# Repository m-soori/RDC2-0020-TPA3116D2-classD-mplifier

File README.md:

<p></p>

<p>Усилитель НЧ собран на микросхеме TPA3116D2.</p>
<p></p>
<h2>Технические характеристики.</h2>
<p>Мощность на нагрузке 4 Ом. при U пит. 21В. – 2 x 50 Вт. (BTL), 100 Вт. (PBTL)<br/>Уровень сигнала на входе. - 0,8 … 2В.<br/>Отношение сигнал/шум. - 102 dB<br/>Коэффициент гармоник на половине мощности 25Вт. -  0,1%<br/>Напряжение питания – 4,5 В … 26 В.</p>
<p>Схема позволяет включать микросхему в двух режимах: </p>
<p>1. Мостовой BTL. В этом включении можно получить 2 канала по 50 Вт.<br/>2. Параллельно – мостовой (PBTL). Так как в этом режиме два канала BTL включены ещё и параллельно, то на выходе получаем один канал с удвоенной мощностью – 100 Вт.</p>
<p>На схемах ниже показаны все необходимые изменения для обоих режимов. </p>
<p>1. Подготовка платы для работы в мостовом режиме. Стерео 50 Вт.<br/>Собранный усилитель работает в мостовом режиме. Но если вы подаете на него сигнал по не симметричной линии, установите перемычки P7 и P12. Больше никаких перемычек устанавливать не надо. </p>
<p>2. Подготовка платы для работы в параллельно-мостовом режиме. Один канал 100 Вт.<br/>Установите перемычки P14, P15 и соедините перемычкой выходы усилителя P3 с P4 и P8 с P11.<br/>Теперь ваш усилитель будет работать в параллельно-мостовом режиме и выдавать 100 Вт.  Громкоговоритель подключайте к P6 и P8. Сигнал подавайте на вход правого канала.</p>
<p>Режим BTL</p>
<p></p>
<p>Режим PBTL</p>
<p></p>
<p>Подбором резисторов R5 и R8 можно подобрать уровень усиления и входное сопротивление, а также перевести усилитель в режимы ведущего (master) или ведомого (slave)</p>
<p></p>
<p>Усилитель имеет очень высокий КПД > 90%, поэтому он не очень требователен к теплоотводу. В качестве радиатора можно использовать, <a href="/product0/9000398392" class="link">например этот</a>. Форма, крепежные отверстия и размеры, которого сделаны специально для этого модуля. К тому же он имеет золотое покрытие, что внешне очень привлекательно.</p>
<p>Радиатор</p>
<p></p>
<p>Это открытый проект! Лицензия, под которой он распространяется – <a href="https://creativecommons.org/licenses/by-sa/3.0/"  class="link">Creative Commons - Attribution - Share Alike</a> license.</p>

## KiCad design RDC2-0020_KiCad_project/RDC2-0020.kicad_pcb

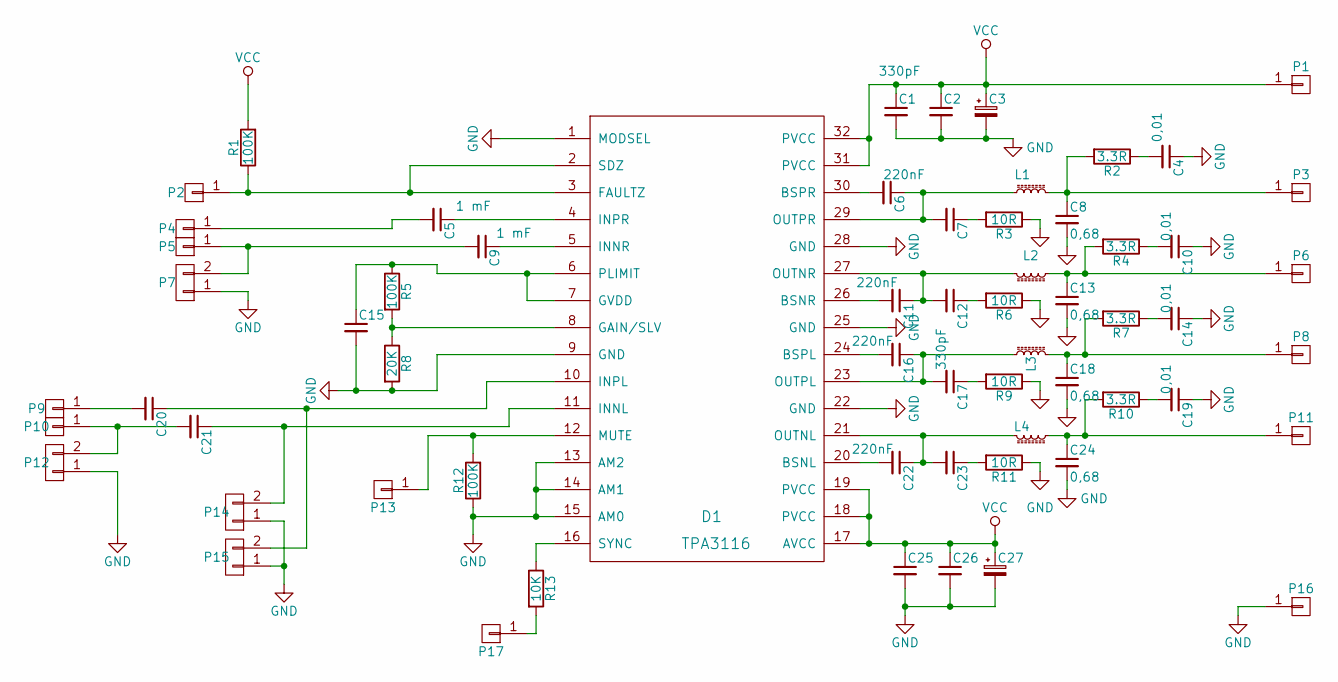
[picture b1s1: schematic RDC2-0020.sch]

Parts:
C1, C7, C12, C17, C23, C25: 330pF; C_1206
C2, C26: 0,1; C_0603
C3: 220mF; C_Radial_D8_L11.5_P3.5
C4, C10, C14, C19: 0,01; C_0805
C5, C9: 1 mF; C_0603
C6, C11, C16, C22: 220nF; C_0805
C8, C13, C18, C24: 0,68; C_1206
C15: C_Small; C_0805
C20, C21: C_Small; C_0603
C27: 220pF; C_Radial_D8_L11.5_P3.5
D1: TPA3116; TSSOP32
L1, L2, L3, L4: L_Core_Ferrite_Small; IND_12x12mm_h6mm
P1, P16: CONN_01X01; MountingHole_3.2mm_M3_Pad
P2, P3, P4, P5, P6, P8, P9, P10, P11, P13, P17: CONN_01X01; Pin_Header_Straight_1x01
P7, P12, P14, P15: CONN_01X02; JUMPER_ON
R1, R5, R12: 100K; R_0603
R2, R4, R7, R10: 3.3R; R_0603
R3, R6, R9, R11: 10R; R_0603
R8: 20K; R_0603
R13: 10K; R_0603

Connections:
GND: C1.2, C2.2, C3.2, C4.1, C8.2, C10.1, C13.2, C14.1, C15.2, C18.2, C19.1, C24.2, C25.2, C26.2, C27.2, D1.1 (MODSEL), D1.9 (GND), D1.13 (AM2), D1.14 (AM1), D1.15 (AM0), D1.22 (GND), D1.25 (GND), D1.28 (GND), P7.1, P12.1, P14.1, P15.1, P16.1, R3.1, R6.1, R8.2, R9.1, R11.1, R12.1
unnamed: C4.2, R2.1
unnamed: C5.1, D1.4 (INPR)
unnamed: C5.2, P4.1
unnamed: C6.1, C7.2, D1.29 (OUTPR), L1.1
unnamed: C6.2, D1.30 (BSPR)
unnamed: C7.1, R3.2
unnamed: C8.1, L1.2, P3.1, R2.2
unnamed: C9.1, D1.5 (INNR)
unnamed: C9.2, P5.1, P7.2
unnamed: C10.2, R4.1
unnamed: C11.1, C12.2, D1.27 (OUTNR), L2.2
unnamed: C11.2, D1.26 (BSNR)
unnamed: C12.1, R6.2
unnamed: C13.1, L2.1, P6.1, R4.2
unnamed: C14.2, R7.1
unnamed: C15.1, D1.6 (PLIMIT), D1.7 (GVDD), R5.1
unnamed: C16.1, C17.2, D1.23 (OUTPL), L3.1
unnamed: C16.2, D1.24 (BSPL)
unnamed: C17.1, R9.2
unnamed: C18.1, L3.2, P8.1, R7.2
unnamed: C19.2, R10.1
unnamed: C20.1, D1.10 (INPL), P15.2
unnamed: C20.2, P9.1
unnamed: C21.1, D1.11 (INNL), P14.2
unnamed: C21.2, P10.1, P12.2
unnamed: C22.1, C23.2, D1.21 (OUTNL), L4.2
unnamed: C22.2, D1.20 (BSNL)
unnamed: C23.1, R11.2
unnamed: C24.1, L4.1, P11.1, R10.2
unnamed: D1.2 (SDZ), D1.3 (FAULTZ), P2.1, R1.1
unnamed: D1.8 (GAIN/SLV), R5.2, R8.1
unnamed: D1.12 (MUTE), P13.1, R12.2
unnamed: D1.16 (SYNC), R13.1
unnamed: P17.1, R13.2
VCC: C1.1, C2.1, C3.1, C25.1, C26.1, C27.1, D1.17 (AVCC), D1.18 (PVCC), D1.19 (PVCC), D1.31 (PVCC), D1.32 (PVCC), P1.1, R1.2

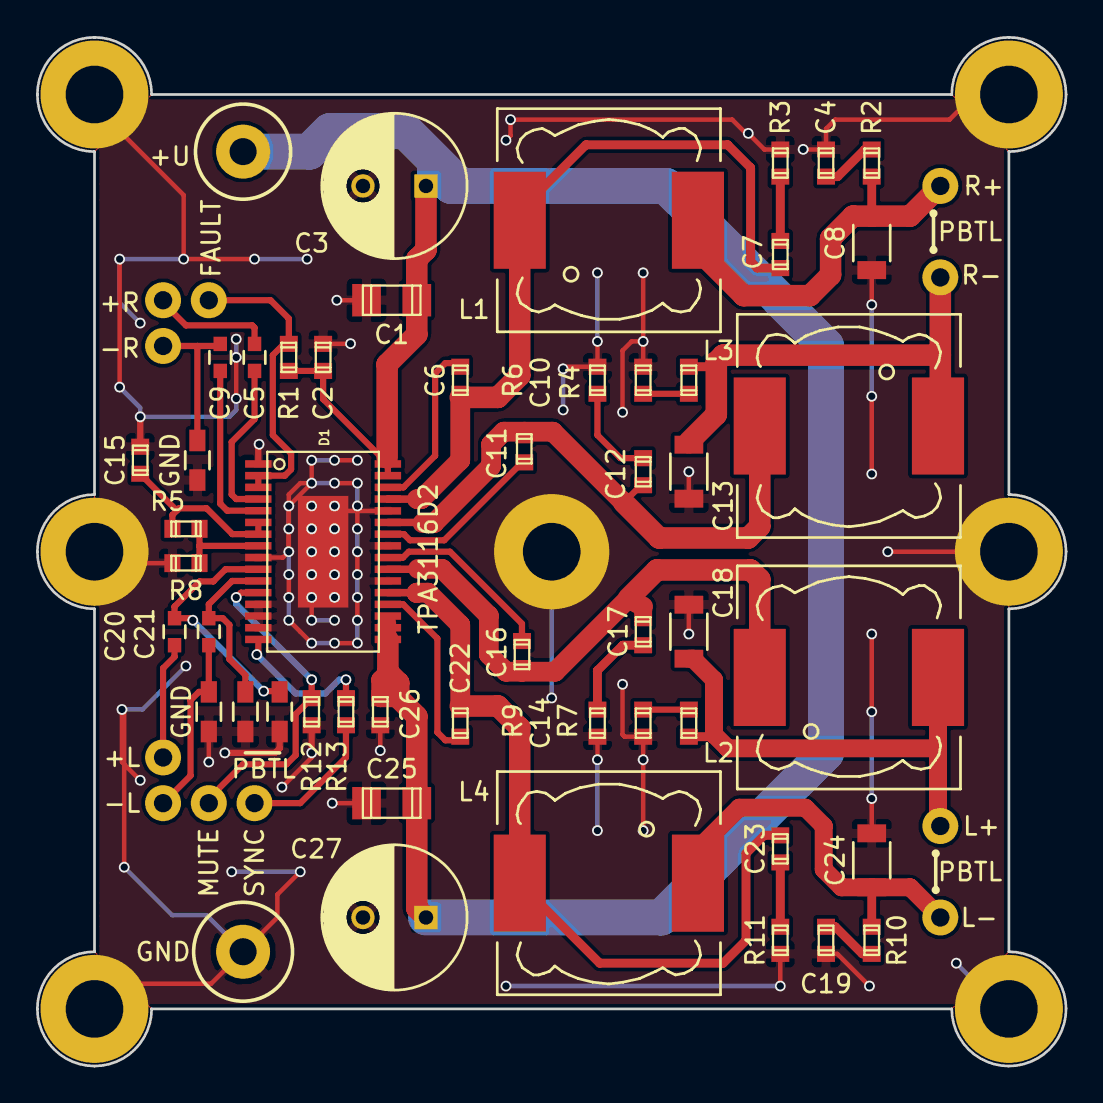
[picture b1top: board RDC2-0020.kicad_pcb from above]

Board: 2 copper layers, 57.2 x 57.2 mm, 62 parts (0 on the bottom side), 36 nets.

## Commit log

2018-09-27 KiCad project
2018-09-27 Gerber files
